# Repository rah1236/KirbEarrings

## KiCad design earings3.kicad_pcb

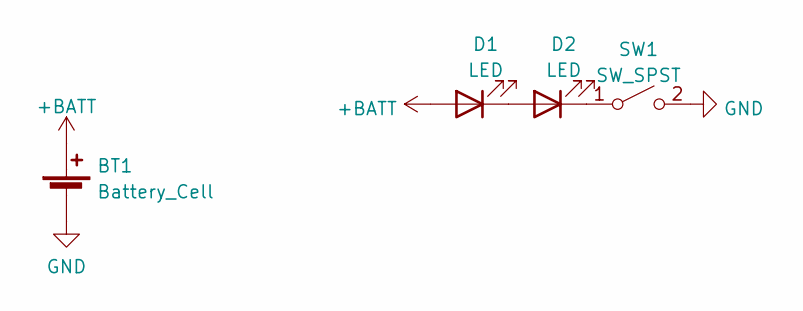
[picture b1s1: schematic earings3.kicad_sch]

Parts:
BT1: Battery_Cell; BatteryHolder_Keystone_2998_1x6.8mm
D1, D2: LED; LED_Kingbright_APFA3010_3x1.5mm_Horizontal
SW1: SW_SPST; SW_DIP_SPSTx01_Slide_6.7x4.1mm_W6.73mm_P2.54mm_LowProfile_J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

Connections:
+BATT: BT1.1 (+), D1.2 (A)
GND: BT1.2 (-), SW1.2 (B)
unnamed: D1.1 (K), D2.2 (A)
unnamed: D2.1 (K), SW1.1 (A)

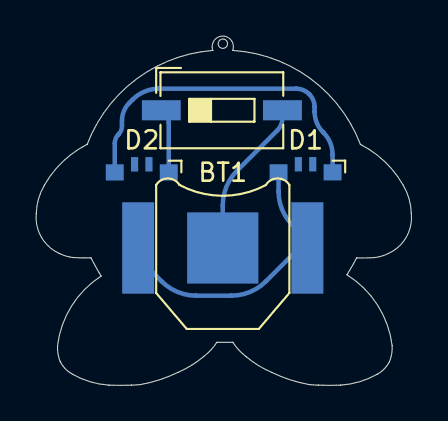
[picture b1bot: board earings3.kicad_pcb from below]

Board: 2 copper layers, 20.9 x 19.4 mm, 4 parts (4 on the bottom side), 4 nets.
